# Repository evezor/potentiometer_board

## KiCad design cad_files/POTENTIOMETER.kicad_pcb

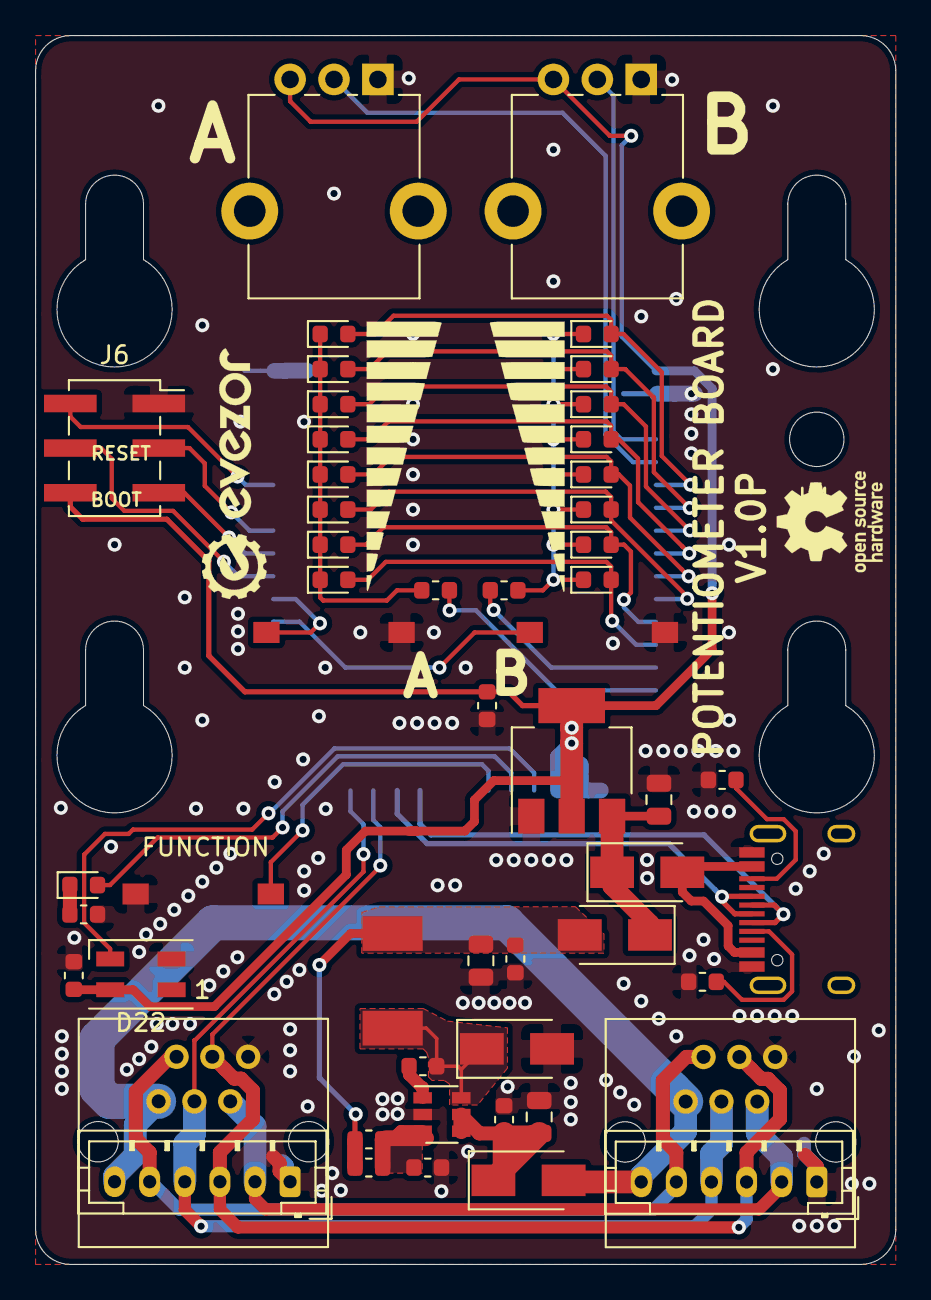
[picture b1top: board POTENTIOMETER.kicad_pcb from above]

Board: 2 copper layers, 49.0 x 70.0 mm, 54 parts (1 on the bottom side), 42 nets.

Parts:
C1, C2, C3, C5, C9: .1uF; C_0603_1608Metric
C4: 4.7uF; C_0805_2012Metric
C6: 22uF; C_0805_2012Metric
C7: 10uF; C_0805_2012Metric
C10: C_Small; C_0603_1608Metric
D1, D2, D3, D4, D5, D6, D7, D8, D9, D10, D11, D12, D13, D14, D15, D16, D21: LED; LED_0603_1608Metric
D17, D18, D19, D20: SX35_SCHOTTKY; D_SMA
D22: SK6812MINI; LED_SK6812MINI_PLCC4_3.5x3.5mm_P1.75mm
H1: MountingHole; OLED_STANDOFF
J1: USB_C_Receptacle_USB2.0; USB_C_Receptacle_HRO_TYPE-C-31-M-12
J2, J3: PH; JST_PH_B6B-PH-K_1x06_P2.00mm_Vertical
J4, J5: RJ11; RJ11_C189747_Horizontal
J6: Conn_02x03_Odd_Even; OLED_HEADER
L1: 22uH; INDUCTOR_7.5X6.6_GCDA0630-220MC
R1, R2: TBD; R_0603_1608Metric
R3, R8: 15k; R_0603_1608Metric
R4: 82k; R_0603_1608Metric
R5, R6: 5.1k; R_0603_1608Metric
RV1, RV2: POT; Potentiometer_Alpha_RD901F-40-00D_Single_Vertical_CircularH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
SW1, SW2, SW3: SW_Push; SWITCH_2x3_SMD_TACTILE_GREEN
U1: SY8401ABC; SOT-23-6
U2: EDGE_STM32F405_CPU_V1; EDGE_STAMP
U3: AMS1117-3.3; SOT-223-3_TabPin2

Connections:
+3V3: C9.1, C10.2, D22.4, J6.6, RV1.3, RV2.3, U2.1, U2.18, U3.2
/BOOT: J6.3, U2.36
/BUT_A: SW1.1, U2.33
/BUT_B: SW2.1, U2.32
/CAN_H: J2.3, J3.3, J4.3, J5.3, U2.26
/CAN_L: J2.4, J3.4, J4.4, J5.4, U2.27
/CC1: J1.A5, R6.1
/CC2: J1.B5, R5.1
/COLUMN_1: R1.2, U2.15
/COLUMN_2: R2.2, U2.14
/D+: J1.A6, J1.B6, U2.25
/D-: J1.A7, J1.B7, U2.24
/FD_H: J2.2, J3.2, J4.2, J5.2
/FD_L: J2.5, J3.5, J4.5, J5.5
/FUNCTION_BUTTON: SW3.1, U2.21
/HBT_LED: D21.2, U2.20
/NEO_STATUS: D22.3, U2.19
/OLED_SCL: J6.5, U2.35
/OLED_SDA: J6.4, U2.34
/POT_A: RV1.2, U2.4
/POT_B: RV2.2, U2.5
/RESET: J6.2, U2.38
/ROW_1: D1.2, D9.2, U2.6
/ROW_2: D2.2, D10.2, U2.7
/ROW_3: D3.2, D11.2, U2.8
/ROW_4: D4.2, D12.2, U2.9
/ROW_5: D5.2, D13.2, U2.10
/ROW_6: D6.2, D14.2, U2.11
/ROW_7: D7.2, D15.2, U2.12
/ROW_8: D8.2, D16.2, U2.13
/USB_VCC: D19.2, J1.A4, J1.A9, J1.B4, J1.B9
/VREG_OUT: C2.1, C5.1, C6.1, D20.2, L1.2, R4.1
GND: C3.2, C4.2, C5.2, C6.2, C7.2, C9.2, C10.1, D17.2, D22.2, J1.A1, J1.A12, J1.B1, J1.B12, J2.1, J3.1, J4.1, J5.1, J6.1, R3.1, R5.2, R6.2, R8.1, RV1.1, RV2.1, SW1.2, SW2.2, SW3.2, U1.2, U2.2, U2.17, U2.43, U3.1
unnamed: C1.1, D17.1, L1.1, U1.6
unnamed: C1.2, U1.1
unnamed: C2.2, R3.2, R4.2, U1.3
unnamed: C3.1, C4.1, D18.1, U1.4, U1.5
unnamed: C7.1, D19.1, D20.1, U3.3
unnamed: D1.1, D2.1, D3.1, D4.1, D5.1, D6.1, D7.1, D8.1, R1.1
unnamed: D9.1, D10.1, D11.1, D12.1, D13.1, D14.1, D15.1, D16.1, R2.1
unnamed: D21.1, R8.2
VBUS: D18.2, J2.6, J3.6, J4.6, J5.6

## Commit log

2020-11-06 first
2020-11-06 add schematic
2020-11-15 add message received animation
